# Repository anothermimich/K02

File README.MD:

**Less, but better.** - Dieter Rams

After seeing the [Ferris Sweep](https://github.com/davidphilipbarr/Sweep) for the first time I've fallen in love, but as a designer I cannot accept things the way they are. So I've done some experimentation with it. I changed the overall form of the board so it can be a little bit more compact and be a canvas for expression in the matter of case design.

This is a parcial redesign of the [Ferris Sweep 2 half-swept](https://github.com/davidphilipbarr/Sweep). In other words this is a:

- 34 keys.
- Diodeless.
- Low profile.
- Non-hotswap.
- Reversible PCB.
- Column staggered.
- [Tenting puck](https://splitkb.com/products/tenting-puck) compatible.
- Wireless and wired capable.
- Choc MBK spaced (17,5mm x 16,5mm).
- Cheaper than the [cheapino](https://github.com/tompi/cheapino) (at the time of the build).

### What have been done:

- Change PCB overall form.
- Add support screw holes.
- Create an [assembly manual](/other/manuals/k02-assembly-manual.pdf).
- Add teardrop on solder joints.
- Reposition of the reset and power switch.
- Create an alternative version with `USB-C` instead of `TRRS`.
- Add commissioned art by the brazilian artist [Aline Dal Pont](https://www.instagram.com/manifesto.efemero/).
- Remove all the informative silk graphics for a better looking board.

### What I may do<sup>1</sup>:

- Rotate the main switches.
- Change the `USB-C` location.
- Add open hardware logo on silk.
- Make it compatible with choc V2 switches.
- Design some _minimalist_ and _low profile_ cases.

> <sup>1</sup> The main reason for not doing this at the moment is the lack of financial motivation. As I have to pay for every prototype and take time off to do the development and iterations I have to be mindful of the tasks I take. If you want to help [buy me a coffee](https://ko-fi.com/luimmich) or [contact me](https://www.reddit.com/user/kynikoi_/) :)

## Silk art

I commissioned the work of the brazilian artist [Aline Dal Pont](https://www.instagram.com/manifesto.efemero/) for this board. You can use it as it is (with the credits) for non-commercial ends. You cannot use the work outside of this board, modify it in any way or use it commercially without the express autorization of the artist.

## Versions

The `rev. 01` contains 2 versions, one with `TRRS` and one with `USB-C` connecting the halves<sup>2</sup>.

The `rev. 02` are under development. It will introduce an choc V1 and V2 hybrid version of the `USB-C` version.

> <sup>2</sup> The `TRRS` connector are objectively worse than the `USB-C` for this use case, due to it introducing a risk of short in the case that the halves are unpluged with the board powered on. On the other side, the `USB-C` if not wired correctly may introduce a [risk of being connected directly to a power supply](https://docs.qmk.fm/features/split_keyboard) by mistake. I've done the bare minimum to prevent it, I wired the `GND` and `VCC` trying to follow the USB protocol. Another problem with the `USB-C` is that this implementation doesn't follow the USB protocol, it just hijack some of the data pins.

The [gerber files are in the release section.](https://github.com/anothermimich/K02/releases)
The detailed list of materials for each version are inside of the respective folder.

## Assembly

As the pcb doesn't have any information guiding the assembly, I have done an [assembly manual with visual instructions](/other/manuals/k02-assembly-manual.pdf).

## Keymap

As the `rev. 01` maintain the pin out of the [Ferris Sweep](https://github.com/davidphilipbarr/Sweep) you can use any compatible keymap/firmware.

Currenty I'm using the above [zmk](https://zmk.dev/) keymap, you can replicate it with [this files](https://github.com/anothermimich/zmk-config-k02).

> I've tried to use the [Miryoku ZMK](https://github.com/manna-harbour/miryoku_zmk) keymap made by [Manna Harbour](https://github.com/manna-harbour), but I was not able to adapt it to my needs. If you want to see my initial setup take a look at the [compiled firmware](/other/old%20miryoku%20keymaps/) or the source [github workflow](https://github.com/anothermimich/miryoku_zmk/blob/master/.github/workflows/workflow-build-k02.yml), [custom_config.h](https://github.com/anothermimich/miryoku_zmk/blob/master/miryoku/custom_config.h), [cradio_left.conf](https://github.com/anothermimich/miryoku_zmk/blob/master/config/cradio_left.conf) and [cradio_right.conf](https://github.com/anothermimich/miryoku_zmk/blob/master/config/cradio_right.conf) files.

## Disclaimer

The files in this repo may contain problems, use them at your own risk.

For the type nerds _(like me)_, the text on the PCB and logo are [FuturaRenner](https://www.fontsquirrel.com/fonts/futura-renner) aka [Formera](https://github.com/noirblancrouge/Formera).

The team behind the design of the incredible [Ferris Sweep](https://github.com/davidphilipbarr/Sweep) are: [Pierre Chevalier](https://github.com/pierrechevalier83), [David Barr](https://github.com/davidphilipbarr), [Ibnu Daru Aji](https://github.com/ibnuda/), [Duccio](https://github.com/duckyb). Without their work this parcial redesign would not be possible.

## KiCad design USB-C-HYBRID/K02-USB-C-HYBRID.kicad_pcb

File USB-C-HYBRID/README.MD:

# Production files

When this version get ready for adoption the [gerber files will be posted in the release section.](https://github.com/anothermimich/K02/releases)

# Necessary Components

| Quantity | What                                                                                                                                                          |
| -------- | ------------------------------------------------------------------------------------------------------------------------------------------------------------- |
| 34       | Switches ([Kailh PG1350/choc V1](https://cdn-shop.adafruit.com/product-files/5113/CHOC+keyswitch_Kailh-CPG135001D01_C400229.pdf) or [Kailh PG1353/choc V2]()) |
| 34       | Keycaps choc spaced                                                                                                                                           |
| 2        | Reset switches (Omron [B3U-1000P(M)](https://omronfs.omron.com/en_US/ecb/products/pdf/en-b3u.pdf))                                                            |
| 4        | Header ([12pin](https://github.com/joric/nrfmicro/wiki/Sockets))                                                                                              |
| 10       | Rubber feet (8mm x 2mm)                                                                                                                                       |

## Wireless

| What | Quantity                                                                     |
| ---- | ---------------------------------------------------------------------------- |
| 2    | Controller ([nrf52840](https://github.com/joric/nrfmicro/wiki/Alternatives)) |
| 2    | Power switches (MSK 12C02)                                                   |
| 2    | Lithium battery ([301230](https://github.com/joric/nrfmicro/wiki/Batteries)) |

## Wired

| What | Quantity                                                                                                                                     |
| ---- | -------------------------------------------------------------------------------------------------------------------------------------------- |
| 2    | Controller ([QMK pro micro compatible mcu](https://github.com/qmk/qmk_firmware/blob/master/docs/compatible_microcontrollers.md))             |
| 1    | USB Cable (depends on the micro-controller used)                                                                                             |
| 2    | USB-C connector ([TYPE-C-31-M-17](https://www.lcsc.com/datasheet/lcsc_datasheet_2410010030_Korean-Hroparts-Elec-TYPE-C-31-M-17_C283540.pdf)) |
| 1    | USB-C to USB-C cable                                                                                                                         |

# Assembly manual

This versions lacks an specific assembly manual, you can use the `rev. 01` [assembly manual](https://github.com/anothermimich/K02/blob/main/other/manuals/k02-assembly-manual.pdf) for now.

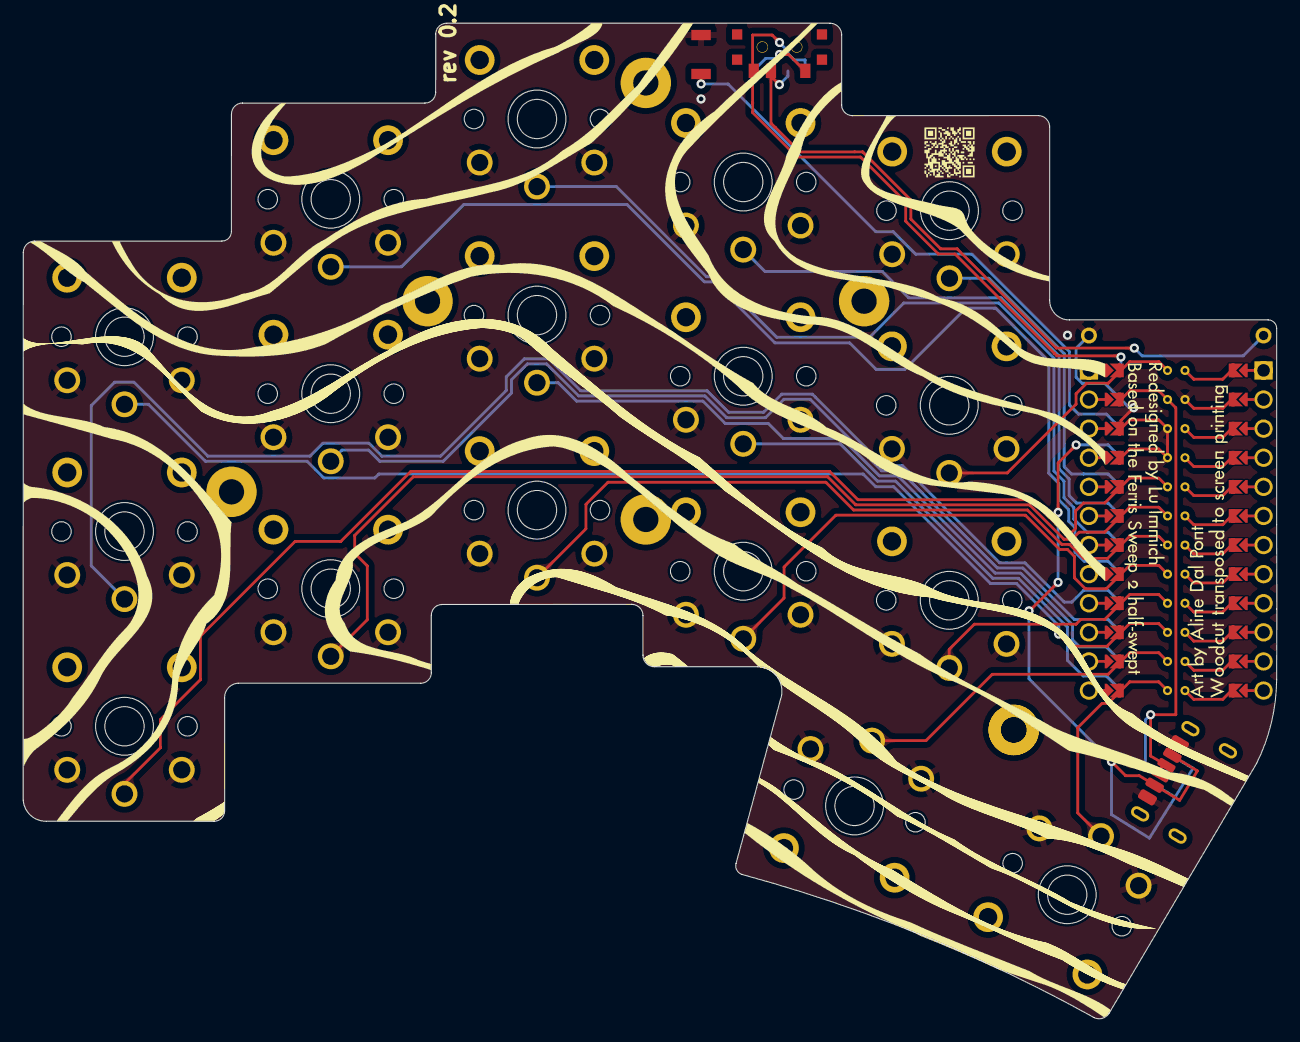
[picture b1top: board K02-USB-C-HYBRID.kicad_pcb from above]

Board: 2 copper layers, 109.4 x 86.9 mm, 22 parts (0 on the bottom side), 21 nets.

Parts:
B+: MountingHole_Pad; 1pin_conn
B-: MountingHole_Pad; 1pin_conn
POWER SW: SW_SPDT; SPDT_C128955
RSW2: SW_Push; Tactile-Switch_SMT
SW1, SW2, SW3, SW4, SW5, SW6, SW7, SW8, SW9, SW10, SW11, SW12, SW13, SW14, SW15, SW16, SW17: SW_Push; choc_v1_v2_rev_inv
U1: ProMicro-kbd; ProMicro_jumpers_facedown

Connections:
BT+_r: B+.1, POWER SW.2
Switch1: SW1.1, U1.10
Switch2: SW2.1, U1.17
Switch3: SW3.1, U1.18
Switch4: SW4.1, U1.19
Switch5: SW5.1, U1.20
Switch6: SW6.1, U1.16
Switch7: SW7.1, U1.15
Switch8: SW8.1, U1.14
Switch9: SW9.1, U1.13
Switch10: SW10.1, U1.1
Switch11: SW11.1, U1.5
Switch12: SW12.1, U1.6
Switch13: SW13.1, U1.7
Switch14: SW14.1, U1.8
Switch15: SW15.1, U1.9
Switch16: SW16.1, U1.11
Switch17: SW17.1, U1.12
gnd: B-.1, RSW2.1, RSW2.2, SW1.2, SW2.2, SW3.2, SW4.2, SW5.2, SW6.2, SW7.2, SW8.2, SW9.2, SW10.2, SW11.2, SW12.2, SW13.2, SW14.2, SW15.2, SW16.2, SW17.2, U1.3, U1.4, U1.23
raw: POWER SW.3, U1.24
reset: RSW2.1, RSW2.2, U1.22

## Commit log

2024-12-26 keymap draw
2024-12-26 keymap readme
2024-12-30 new goals
2024-12-30 update on future things
2024-12-30 keymap
2025-01-03 Update LICENSE
2025-01-03 readme up
2025-01-14 keymap font
2025-01-14 assembly preview
2025-01-14 rename things
2025-01-14 readme
2025-01-14 readme usb c
2025-01-15 hero
2025-01-31 readme update
2025-02-24 readme review
2025-02-24 assembly fix
2025-02-24 manual up
2025-02-25 footprints reversible
2025-02-25 done
2025-02-25 up desc
2025-02-25 rev 02 intro
2025-02-25 readme rev 02
2025-02-25 rev 02
2025-02-25 readme hybrid
2025-02-26 almost there
2025-02-28 test gerber
2025-03-05 battery link
2025-03-13 rev 02 under development
2025-03-13 preparations for rev. 0.2
2025-03-13 upsie
2025-03-14 what
2025-03-15 here we go again
2025-03-28 break the repository
2026-06-07 Revise financial motivation section in README
    Updated financial motivation note with a link to support.
